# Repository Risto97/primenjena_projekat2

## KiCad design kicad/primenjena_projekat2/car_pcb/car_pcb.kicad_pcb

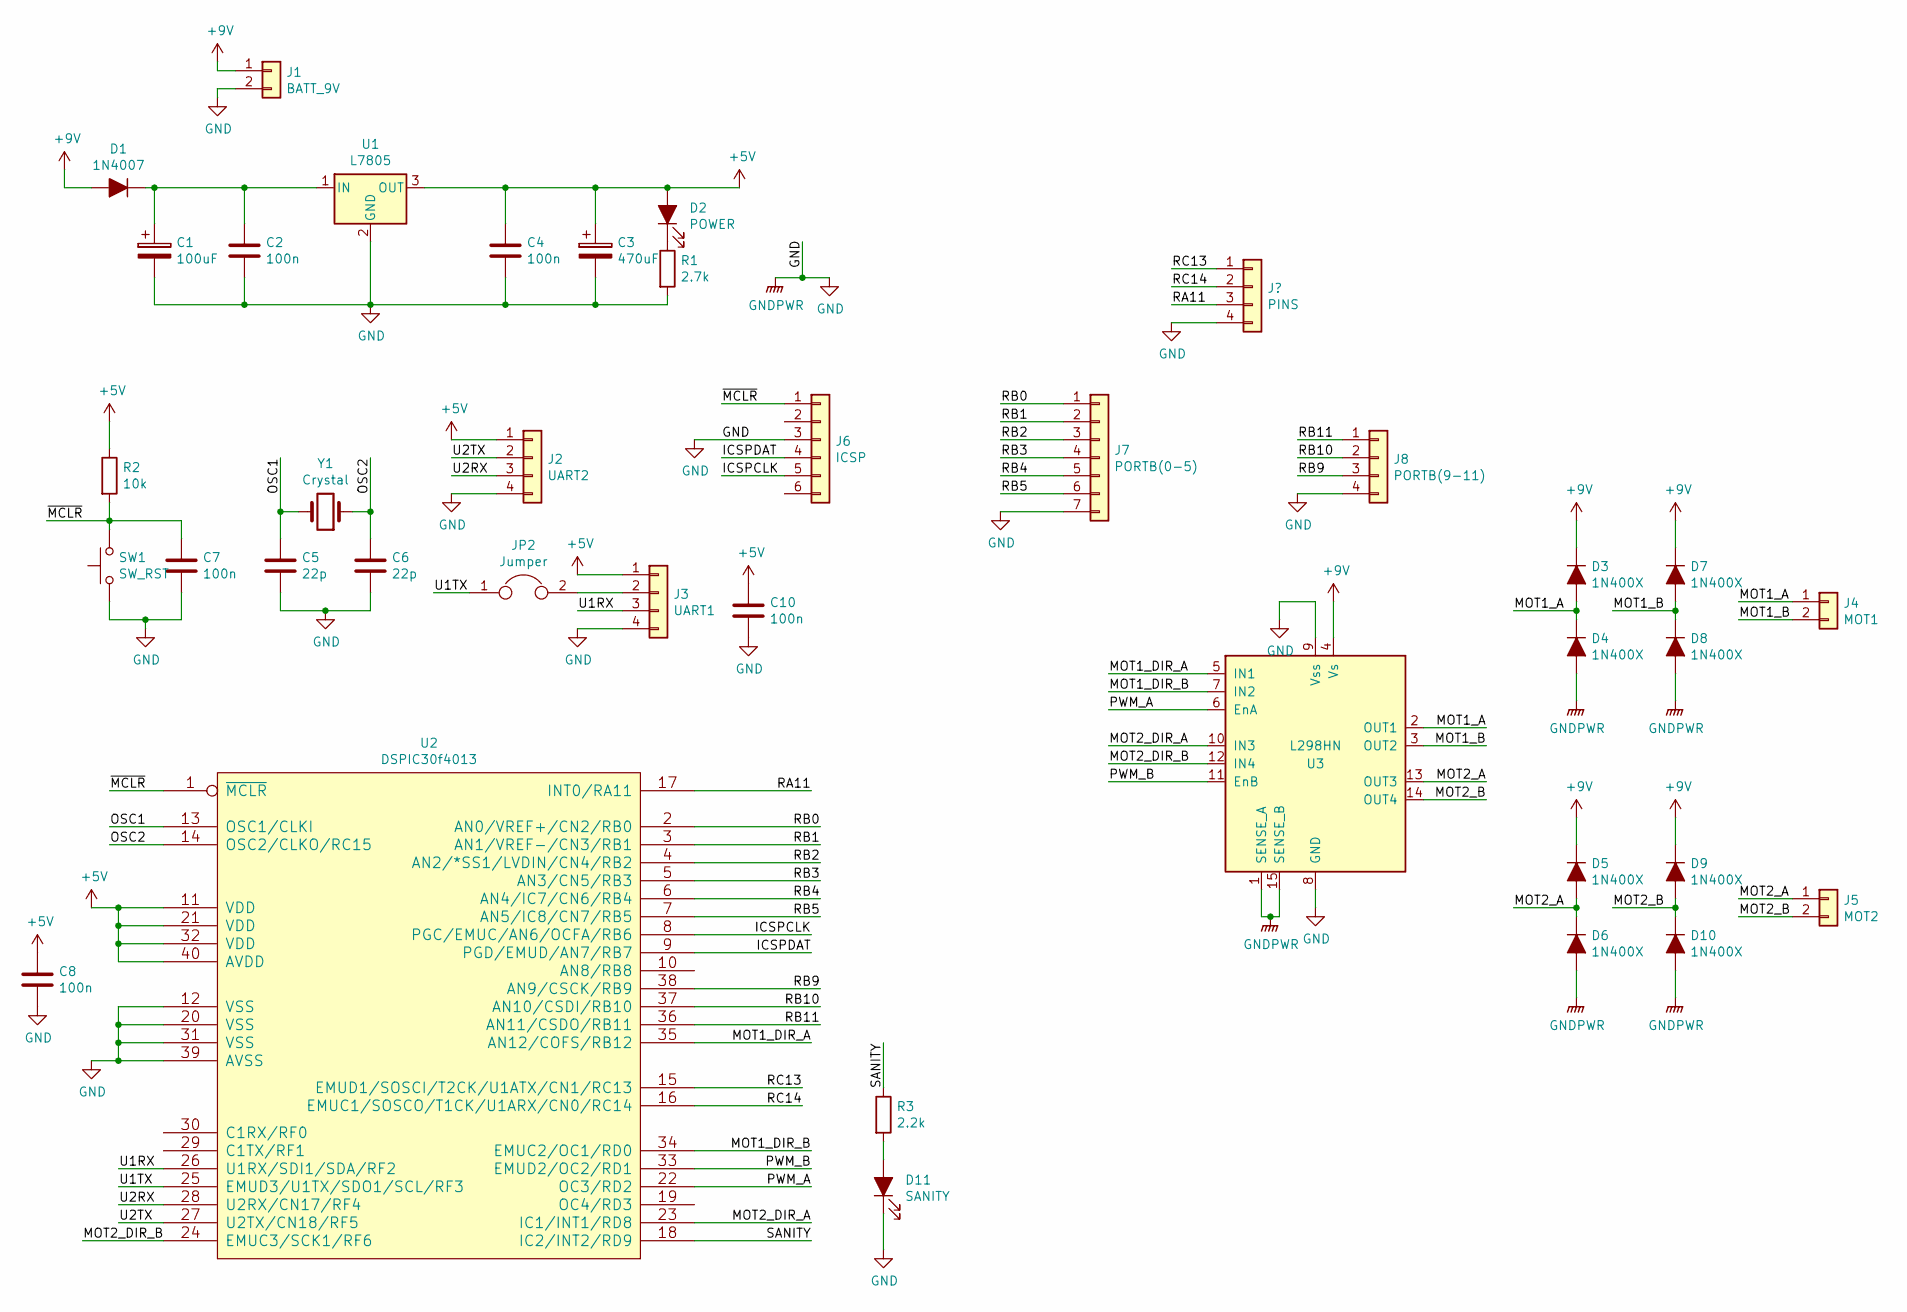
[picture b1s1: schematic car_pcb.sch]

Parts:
C1: 100uF; CP_Radial_D7.5mm_P2.50mm
C2, C4, C7, C8, C10: 100n; C_Disc_D5.0mm_W2.5mm_P5.00mm
C3: 470uF; CP_Radial_D7.5mm_P2.50mm
C5, C6: 22p; C_Disc_D5.0mm_W2.5mm_P2.50mm
D1: 1N4007; D_DO-34_SOD68_P7.62mm_Horizontal
D2: POWER; LED_D5.0mm
D3, D4, D5, D6, D7, D8, D9, D10: 1N400X; D_DO-34_SOD68_P10.16mm_Horizontal
D11: SANITY; LED_D5.0mm
J1: BATT_9V; TerminalBlock_Altech_AK300-2_P5.00mm
J2: UART2; PinHeader_1x04_P2.54mm_Vertical
J3: UART1; PinHeader_1x04_P2.54mm_Vertical
J4: MOT1; TerminalBlock_Altech_AK300-2_P5.00mm
J5: MOT2; TerminalBlock_Altech_AK300-2_P5.00mm
J6: ICSP; PinHeader_1x06_P2.54mm_Vertical
J7: PORTB(0-5); PinHeader_1x07_P2.54mm_Vertical
J8: PORTB(9-11); PinHeader_1x04_P2.54mm_Vertical
JP2: Jumper; PinHeader_1x02_P2.54mm_Vertical
R1: 2.7k; R_Axial_DIN0207_L6.3mm_D2.5mm_P10.16mm_Horizontal
R2: 10k; R_Axial_DIN0207_L6.3mm_D2.5mm_P10.16mm_Horizontal
R3: 2.2k; R_Axial_DIN0207_L6.3mm_D2.5mm_P10.16mm_Horizontal
SW1: SW_RST; SW_PUSH_6mm
U1: L7805; TO-220-3_Vertical
U2: DSPIC30f4013; DIP-40_W15.24mm_LongPads
U3: L298HN; TO-220-15_P2.54x2.54mm_StaggerOdd_Lead4.58mm_Vertical
Y1: Crystal; Crystal_HC50_Vertical

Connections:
+5V: C3.1, C4.1, C8.1, C10.1, D2.2 (A), J2.1, J3.1, R2.1, U1.3 (OUT), U2.11 (VDD), U2.21 (VDD), U2.32 (VDD), U2.40 (AVDD)
+9V: D1.2 (A), D3.1 (K), D5.1 (K), D7.1 (K), D9.1 (K), J1.1, U3.4 (Vs)
/ICSPCLK: J6.5, U2.8 (PGC/EMUC/AN6/OCFA/RB6)
/ICSPDAT: J6.4, U2.9 (PGD/EMUD/AN7/RB7)
/MOT1_A: D3.2 (A), D4.1 (K), J4.1, U3.2 (OUT1)
/MOT1_B: D7.2 (A), D8.1 (K), J4.2, U3.3 (OUT2)
/MOT1_DIR_A: U2.35 (AN12/COFS/RB12), U3.5 (IN1)
/MOT1_DIR_B: U2.34 (EMUC2/OC1/RD0), U3.7 (IN2)
/MOT2_A: D5.2 (A), D6.1 (K), J5.1, U3.13 (OUT3)
/MOT2_B: D9.2 (A), D10.1 (K), J5.2, U3.14 (OUT4)
/MOT2_DIR_A: U2.23 (IC1/INT1/RD8), U3.10 (IN3)
/MOT2_DIR_B: U2.24 (EMUC3/SCK1/RF6), U3.12 (IN4)
/OSC1: C5.1, U2.13 (OSC1/CLKI), Y1.2
/OSC2: C6.1, U2.14 (OSC2/CLKO/RC15), Y1.1
/PWM_A: U2.22 (OC3/RD2), U3.6 (EnA)
/PWM_B: U2.33 (EMUD2/OC2/RD1), U3.11 (EnB)
/RA11: U2.17 (INT0/RA11); also elsewhere on the board
/RB0: J7.1, U2.2 (AN0/VREF+/CN2/RB0)
/RB1: J7.2, U2.3 (AN1/VREF-/CN3/RB1)
/RB2: J7.3, U2.4 (AN2/*SS1/LVDIN/CN4/RB2)
/RB3: J7.4, U2.5 (AN3/CN5/RB3)
/RB4: J7.5, U2.6 (AN4/IC7/CN6/RB4)
/RB5: J7.6, U2.7 (AN5/IC8/CN7/RB5)
/RB9: J8.3, U2.38 (AN9/CSCK/RB9)
/RB10: J8.2, U2.37 (AN10/CSDI/RB10)
/RB11: J8.1, U2.36 (AN11/CSDO/RB11)
/RC13: U2.15 (EMUD1/SOSCI/T2CK/U1ATX/CN1/RC13); also elsewhere on the board
/RC14: U2.16 (EMUC1/SOSCO/T1CK/U1ARX/CN0/RC14); also elsewhere on the board
/SANITY: R3.1, U2.18 (IC2/INT2/RD9)
/U1RX: J3.3, U2.26 (U1RX/SDI1/SDA/RF2)
/U1TX: JP2.1, U2.25 (EMUD3/U1TX/SDO1/SCL/RF3)
/U2RX: J2.3, U2.28 (U2RX/CN17/RF4)
/U2TX: J2.2, U2.27 (U2TX/CN18/RF5)
/~MCLR: C7.1, J6.1, R2.2, SW1.2, U2.1 (~MCLR)
GND: C1.2, C2.2, C3.2, C4.2, C5.2, C6.2, C7.2, C8.2, C10.2, D4.2 (A), D6.2 (A), D8.2 (A), D10.2 (A), D11.1 (K), J1.2, J2.4, J3.4, J6.3, J7.7, J8.4, R1.2, SW1.1, U1.2 (GND), U2.12 (VSS), U2.20 (VSS), U2.31 (VSS), U2.39 (AVSS), U3.1 (SENSE_A), U3.8 (GND), U3.9 (Vss), U3.15 (SENSE_B); also elsewhere on the board
unnamed: C1.1, C2.1, D1.1 (K), U1.1 (IN)
unnamed: D2.1 (K), R1.1
unnamed: D11.2 (A), R3.2
unnamed: J3.2, JP2.2

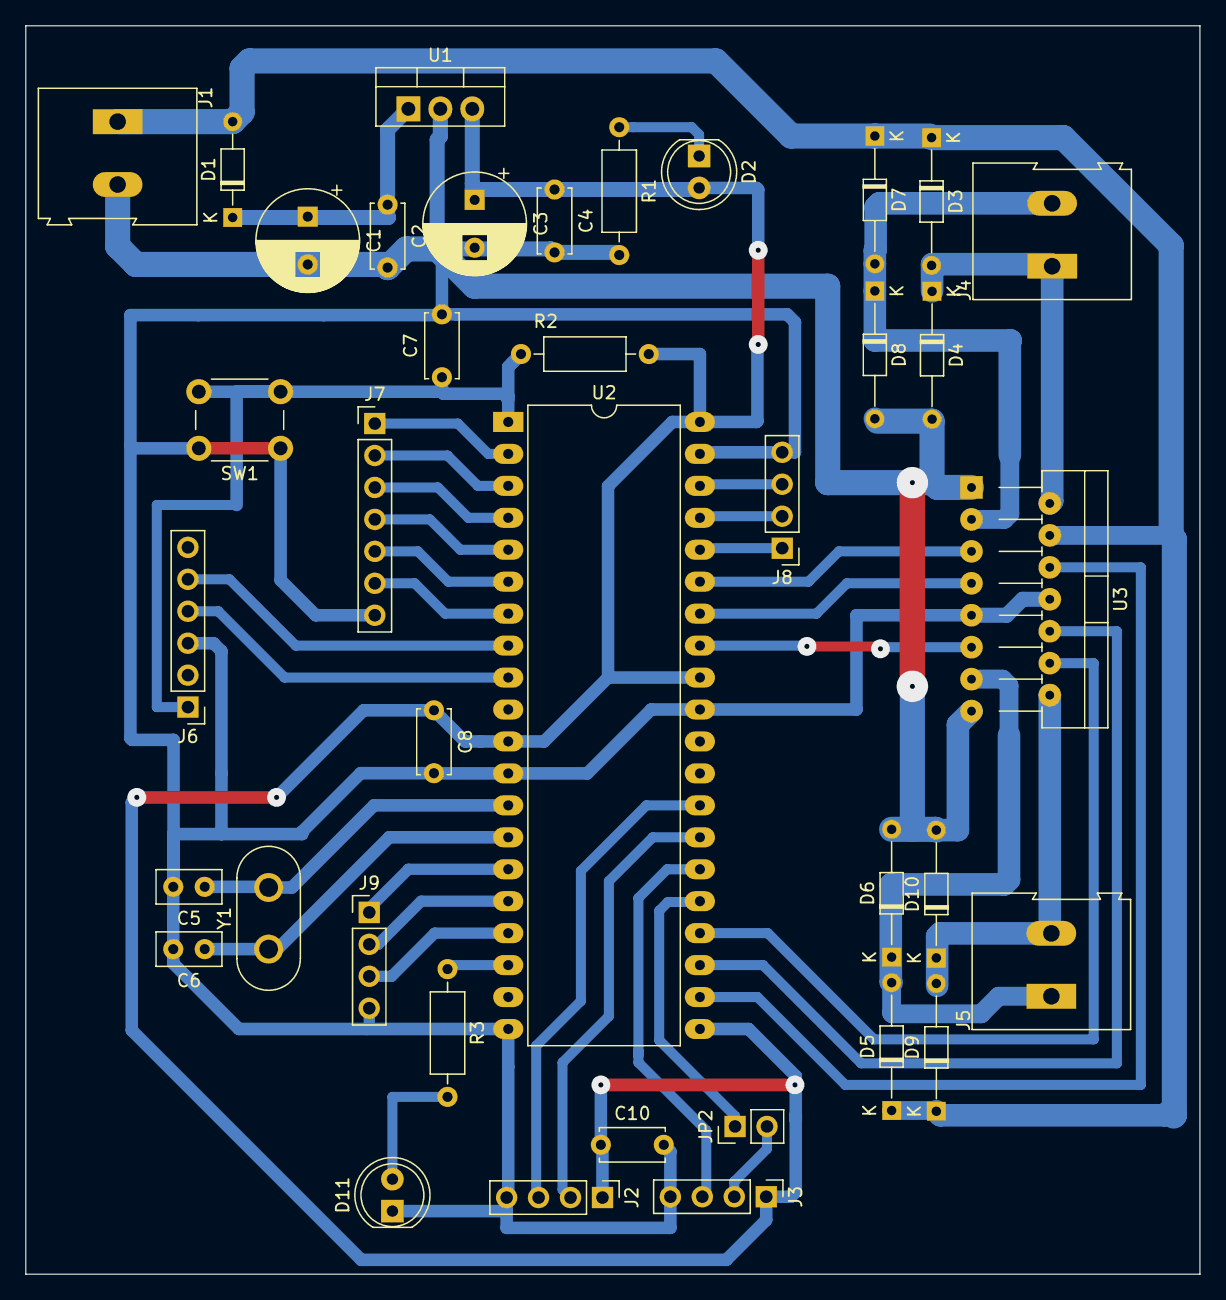
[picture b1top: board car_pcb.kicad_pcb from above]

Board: 2 copper layers, 93.3 x 99.3 mm, 38 parts (0 on the bottom side), 39 nets.

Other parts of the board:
J9: PINS; PinHeader_1x04_P2.54mm_Vertical

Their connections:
/RA11: J9.3; also elsewhere on the board
/RC13: J9.1; also elsewhere on the board
/RC14: J9.2; also elsewhere on the board
GND: J9.4; also elsewhere on the board

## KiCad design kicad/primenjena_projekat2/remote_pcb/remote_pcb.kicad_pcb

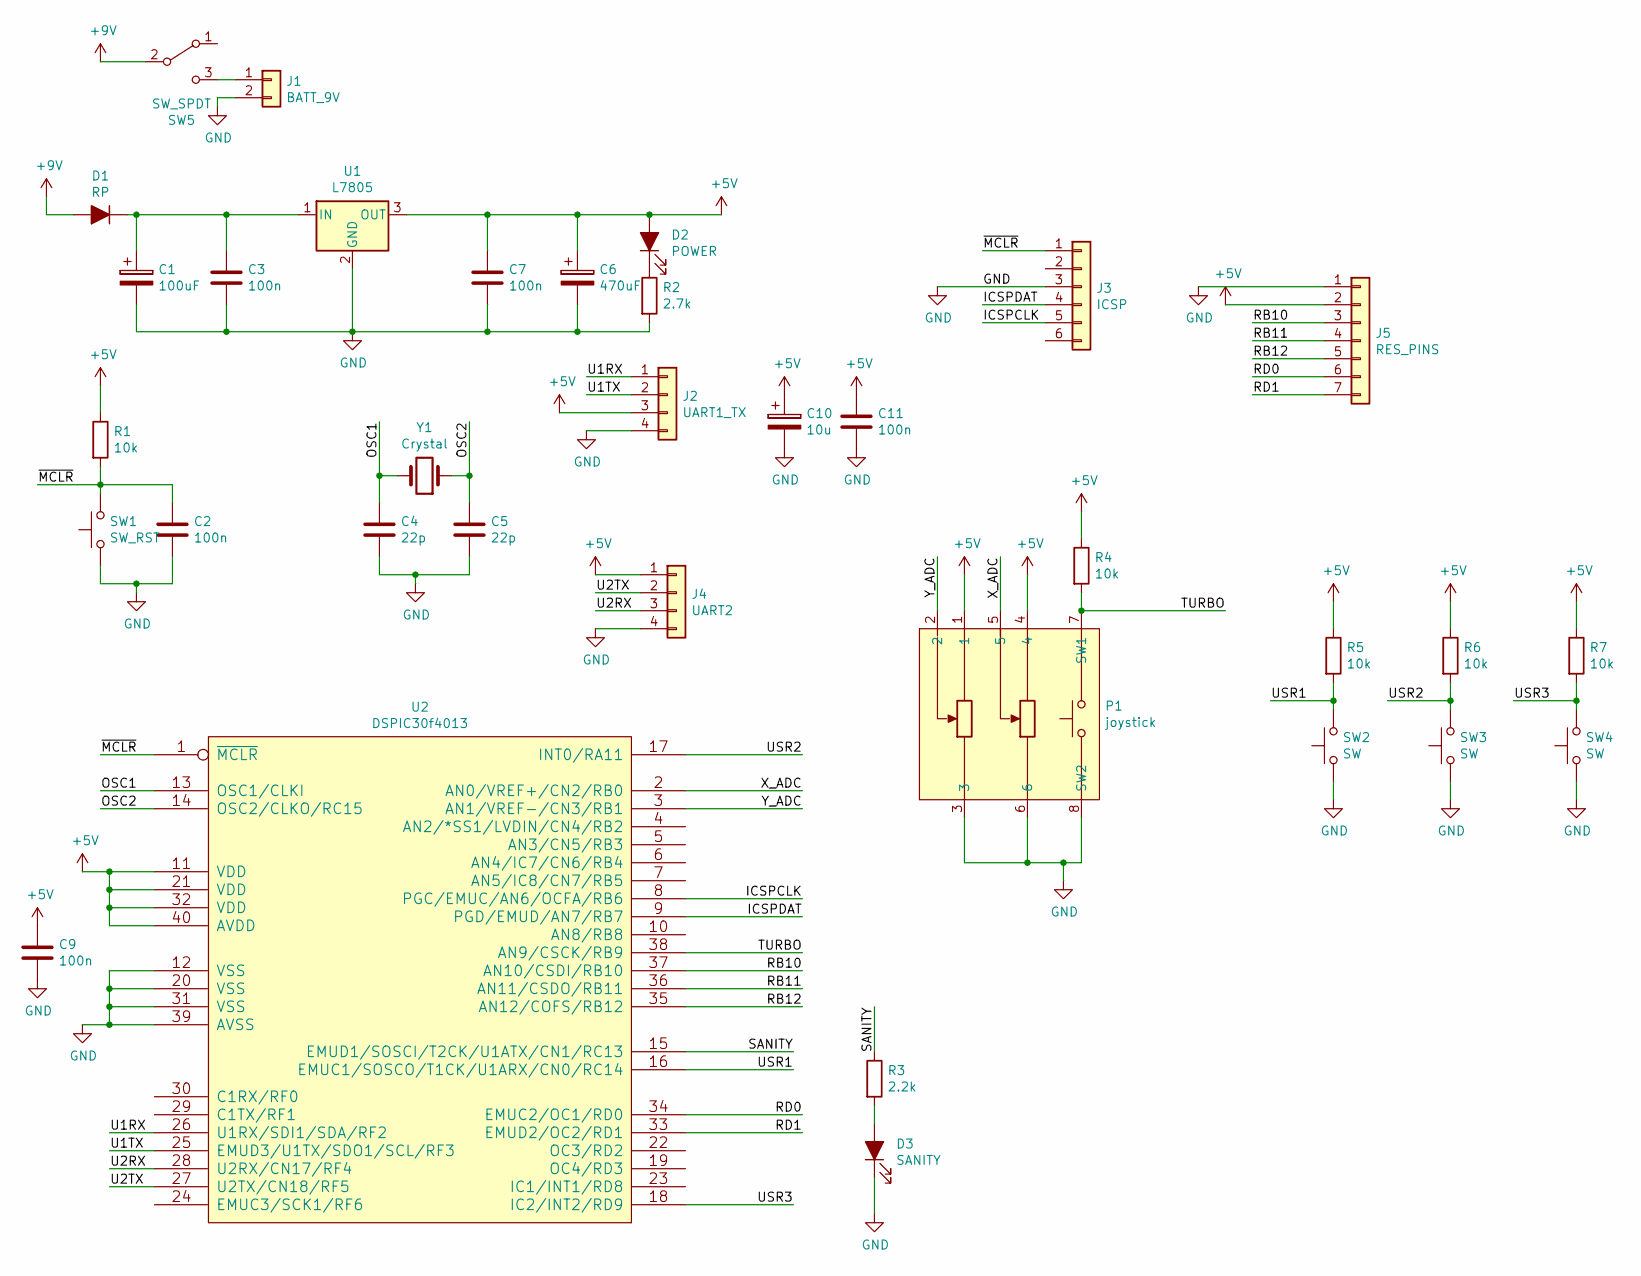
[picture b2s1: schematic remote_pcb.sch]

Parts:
C1: 100uF; CP_Radial_D7.5mm_P2.50mm
C2, C3, C7, C9, C11: 100n; C_Disc_D5.0mm_W2.5mm_P2.50mm
C4, C5: 22p; C_Disc_D5.0mm_W2.5mm_P2.50mm
C6: 470uF; CP_Radial_D7.5mm_P2.50mm
C10: 10u; CP_Radial_D5.0mm_P2.50mm
D1: RP; D_DO-34_SOD68_P7.62mm_Horizontal
D2: POWER; LED_D5.0mm
D3: SANITY; LED_D5.0mm
J1: BATT_9V; TerminalBlock_Altech_AK300-2_P5.00mm
J2: UART1_TX; PinHeader_1x04_P2.54mm_Vertical
J3: ICSP; PinHeader_1x06_P2.54mm_Vertical
J4: UART2; PinHeader_1x04_P2.54mm_Vertical
J5: RES_PINS; PinHeader_1x07_P2.54mm_Vertical
P1: joystick
R1, R4, R5, R6, R7: 10k; R_Axial_DIN0207_L6.3mm_D2.5mm_P10.16mm_Horizontal
R2: 2.7k; R_Axial_DIN0207_L6.3mm_D2.5mm_P10.16mm_Horizontal
R3: 2.2k; R_Axial_DIN0207_L6.3mm_D2.5mm_P10.16mm_Horizontal
SW1: SW_RST; SW_PUSH_6mm
SW2, SW3, SW4: SW; SW_PUSH_6mm
SW5: SW_SPDT; TerminalBlock_RND_205-00068_1x03_P7.50mm_Horizontal
U1: L7805; TO-220-3_Vertical
U2: DSPIC30f4013; DIP-40_W15.24mm_LongPads
Y1: Crystal; Crystal_HC50_Vertical

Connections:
+5V: C6.1, C7.1, C9.1, C10.1, C11.1, D2.2 (A), J2.3, J4.1, J5.2, P1.1, P1.4, R1.1, R4.1, R5.1, R6.1, R7.1, U1.3 (OUT), U2.11 (VDD), U2.21 (VDD), U2.32 (VDD), U2.40 (AVDD)
+9V: D1.2 (A), SW5.2 (B)
/ICSPCLK: J3.5, U2.8 (PGC/EMUC/AN6/OCFA/RB6)
/ICSPDAT: J3.4, U2.9 (PGD/EMUD/AN7/RB7)
/OSC1: C4.1, U2.13 (OSC1/CLKI), Y1.2
/OSC2: C5.1, U2.14 (OSC2/CLKO/RC15), Y1.1
/RB10: J5.3, U2.37 (AN10/CSDI/RB10)
/RB11: J5.4, U2.36 (AN11/CSDO/RB11)
/RB12: J5.5, U2.35 (AN12/COFS/RB12)
/RD0: J5.6, U2.34 (EMUC2/OC1/RD0)
/RD1: J5.7, U2.33 (EMUD2/OC2/RD1)
/SANITY: R3.1, U2.15 (EMUD1/SOSCI/T2CK/U1ATX/CN1/RC13)
/TURBO: P1.7 (SW1), R4.2, U2.38 (AN9/CSCK/RB9)
/U1RX: J2.1, U2.26 (U1RX/SDI1/SDA/RF2)
/U1TX: J2.2, U2.25 (EMUD3/U1TX/SDO1/SCL/RF3)
/U2RX: J4.3, U2.28 (U2RX/CN17/RF4)
/U2TX: J4.2, U2.27 (U2TX/CN18/RF5)
/USR1: R5.2, SW2.2, U2.16 (EMUC1/SOSCO/T1CK/U1ARX/CN0/RC14)
/USR2: R6.2, SW3.2, U2.17 (INT0/RA11)
/USR3: R7.2, SW4.2, U2.18 (IC2/INT2/RD9)
/X_ADC: P1.5, U2.2 (AN0/VREF+/CN2/RB0)
/Y_ADC: P1.2, U2.3 (AN1/VREF-/CN3/RB1)
/~MCLR: C2.1, J3.1, R1.2, SW1.2, U2.1 (~MCLR)
GND: C1.2, C2.2, C3.2, C4.2, C5.2, C6.2, C7.2, C9.2, C10.2, C11.2, D3.1 (K), J1.2, J2.4, J3.3, J4.4, J5.1, P1.3, P1.6, P1.8 (SW2), R2.2, SW1.1, SW2.1, SW3.1, SW4.1, U1.2 (GND), U2.12 (VSS), U2.20 (VSS), U2.31 (VSS), U2.39 (AVSS)
unnamed: C1.1, C3.1, D1.1 (K), U1.1 (IN)
unnamed: D2.1 (K), R2.1
unnamed: D3.2 (A), R3.2
unnamed: J1.1, SW5.3 (C)

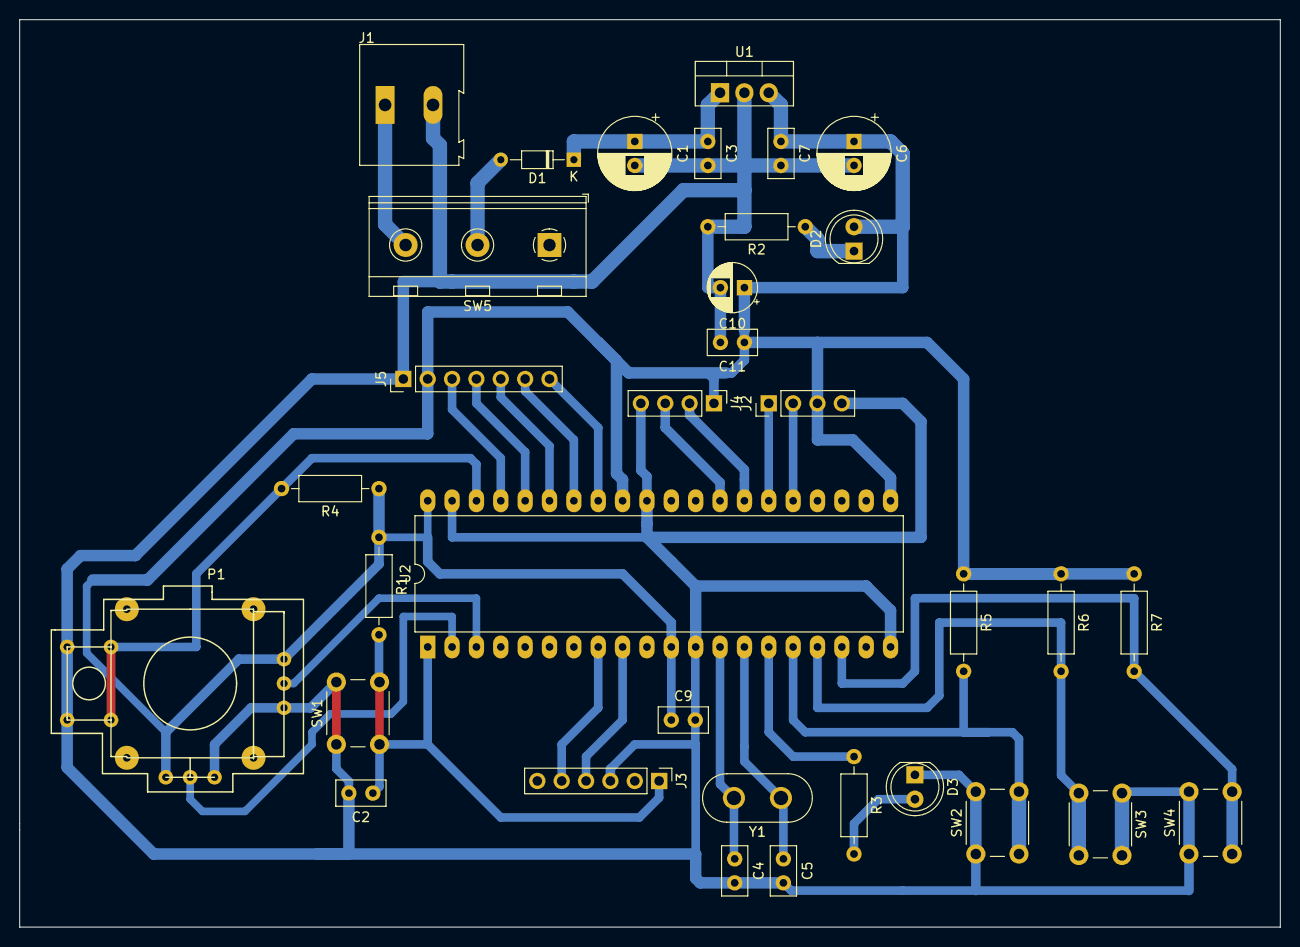
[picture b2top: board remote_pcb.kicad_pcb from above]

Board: 2 copper layers, 131.4 x 94.6 mm, 34 parts (0 on the bottom side), 28 nets.

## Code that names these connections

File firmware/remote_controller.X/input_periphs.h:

#ifndef INPUT_PERIHPS_H
#define INPUT_PERIHPS_H

#include "system.h"        /* System funct/params, like osc/peripheral config */
#include<p30Fxxxx.h>
#include <libpic30.h>

#define TRIS_TURBO TRISBbits.TRISB9
#define ADPCFG_TURBO ADPCFGbits.PCFG9
#define TURBO PORTBbits.RB9

#define TRIS_SANITY TRISCbits.TRISC13
#define SANITY LATCbits.LATC13

#define TRIS_USR1  TRISCbits.TRISC14
#define USR1 PORTCbits.RC14
#define TRIS_USR2  TRISAbits.TRISA11
#define USR2 PORTAbits.RA11
#define TRIS_USR3  TRISDbits.TRISD9
#define USR3 PORTDbits.RD9

#define ADPCFG_JOYSTICK_X ADPCFGbits.PCFG0
#define TRIS_JOYSTICK_X TRISBbits.TRISB0
#define ADPCFG_JOYSTICK_Y ADPCFGbits.PCFG1
#define TRIS_JOYSTICK_Y TRISBbits.TRISB1

void sw_init();
void joystick_init();
void joystick_ADC_start();
void joystick_ADC_stop();
int get_joystickX();
int get_joystickY();
void ADCinit_Joystick(void);

int get_Turbo();
int get_USR1();
int get_USR2();
int get_USR3();

void set_sanity(int value);

#endif

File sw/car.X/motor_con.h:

#ifndef MOTOR_CON_H
#define MOTOR_CON_H

#include "system.h"        /* System funct/params, like osc/peripheral config */
#include<p30Fxxxx.h>
#include <libpic30.h>
#include "commands.h"

#define TRIS_MOT1_DIR_A TRISBbits.TRISB12
#define ADPCFG_MOT1_DIR_A ADPCFGbits.PCFG12
#define MOT1_DIR_A LATBbits.LATB12

#define TRIS_MOT1_DIR_B TRISDbits.TRISD0
#define MOT1_DIR_B LATDbits.LATD0

#define TRIS_MOT2_DIR_A TRISDbits.TRISD8
#define MOT2_DIR_A LATDbits.LATD8

#define TRIS_MOT2_DIR_B TRISFbits.TRISF6
#define MOT2_DIR_B LATFbits.LATF6

#define TRIS_MOT1_EN TRISDbits.TRISD2
#define MOT1_EN LATDbits.LATD2

#define TRIS_MOT2_EN TRISDbits.TRISD1
#define MOT2_EN LATDbits.LATD1

#define TRIS_LIMIT_SW1 TRISCbits.TRISC14
#define LIMIT_SW1 PORTCbits.RC14

#define TRIS_LIMIT_SW2 TRISCbits.TRISC13
#define LIMIT_SW2 PORTCbits.RC13

#define PWM_TIMER_MAX 2500 // ~2khz

void mot1_init();
void mot1_pwm_init();
void mot1_set_duty(unsigned int duty);
void mot1_start(int dir, unsigned int duty);
void _mot1_start();
void mot1_stop();
void mot1_ch_dir(int dir);

void mot2_init();
void mot2_pwm_init();
void mot2_set_duty(unsigned int duty);
void _mot2_start();
void mot2_start(int dir, unsigned int duty);
void mot2_stop();
void mot2_ch_dir(int dir);

void limit_init();

void set_motors(Command_t command);
int speed_to_duty(int speed);

#endif

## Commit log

2019-02-14 change schematic name
2019-02-15 add remote control schematic
2019-02-15 split PCBs
2019-02-19 Remote control PCB
2019-02-22 Add car PCB
2019-03-02 start writing firmware
2019-03-03 firmware
2019-03-03 New software projects
2019-03-03 finish software
2019-03-03 Managed shared files
2019-03-03 Fix steering motor jamming
2019-03-05 Fix stability with RF modules
2019-03-05 Update uart_rf.c
    fix
2019-03-05 Minor cleanup
